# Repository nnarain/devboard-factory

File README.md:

# Dev boards and breakouts

This repo contains KiCAD projects for various dev boards and break outs

| Board    | Description          | Fabricated |
| -----    | -----------          | ---------- |
| xdevrf01 | STM32 + nRF24 module | No         |
| xdevrf02 | nRF52 + PCB Antenna  | No         |
| xdevrf03 | ESP32-C3-MINI        | Yes        |
| brkcan01 | SN65HVD232           | No         |

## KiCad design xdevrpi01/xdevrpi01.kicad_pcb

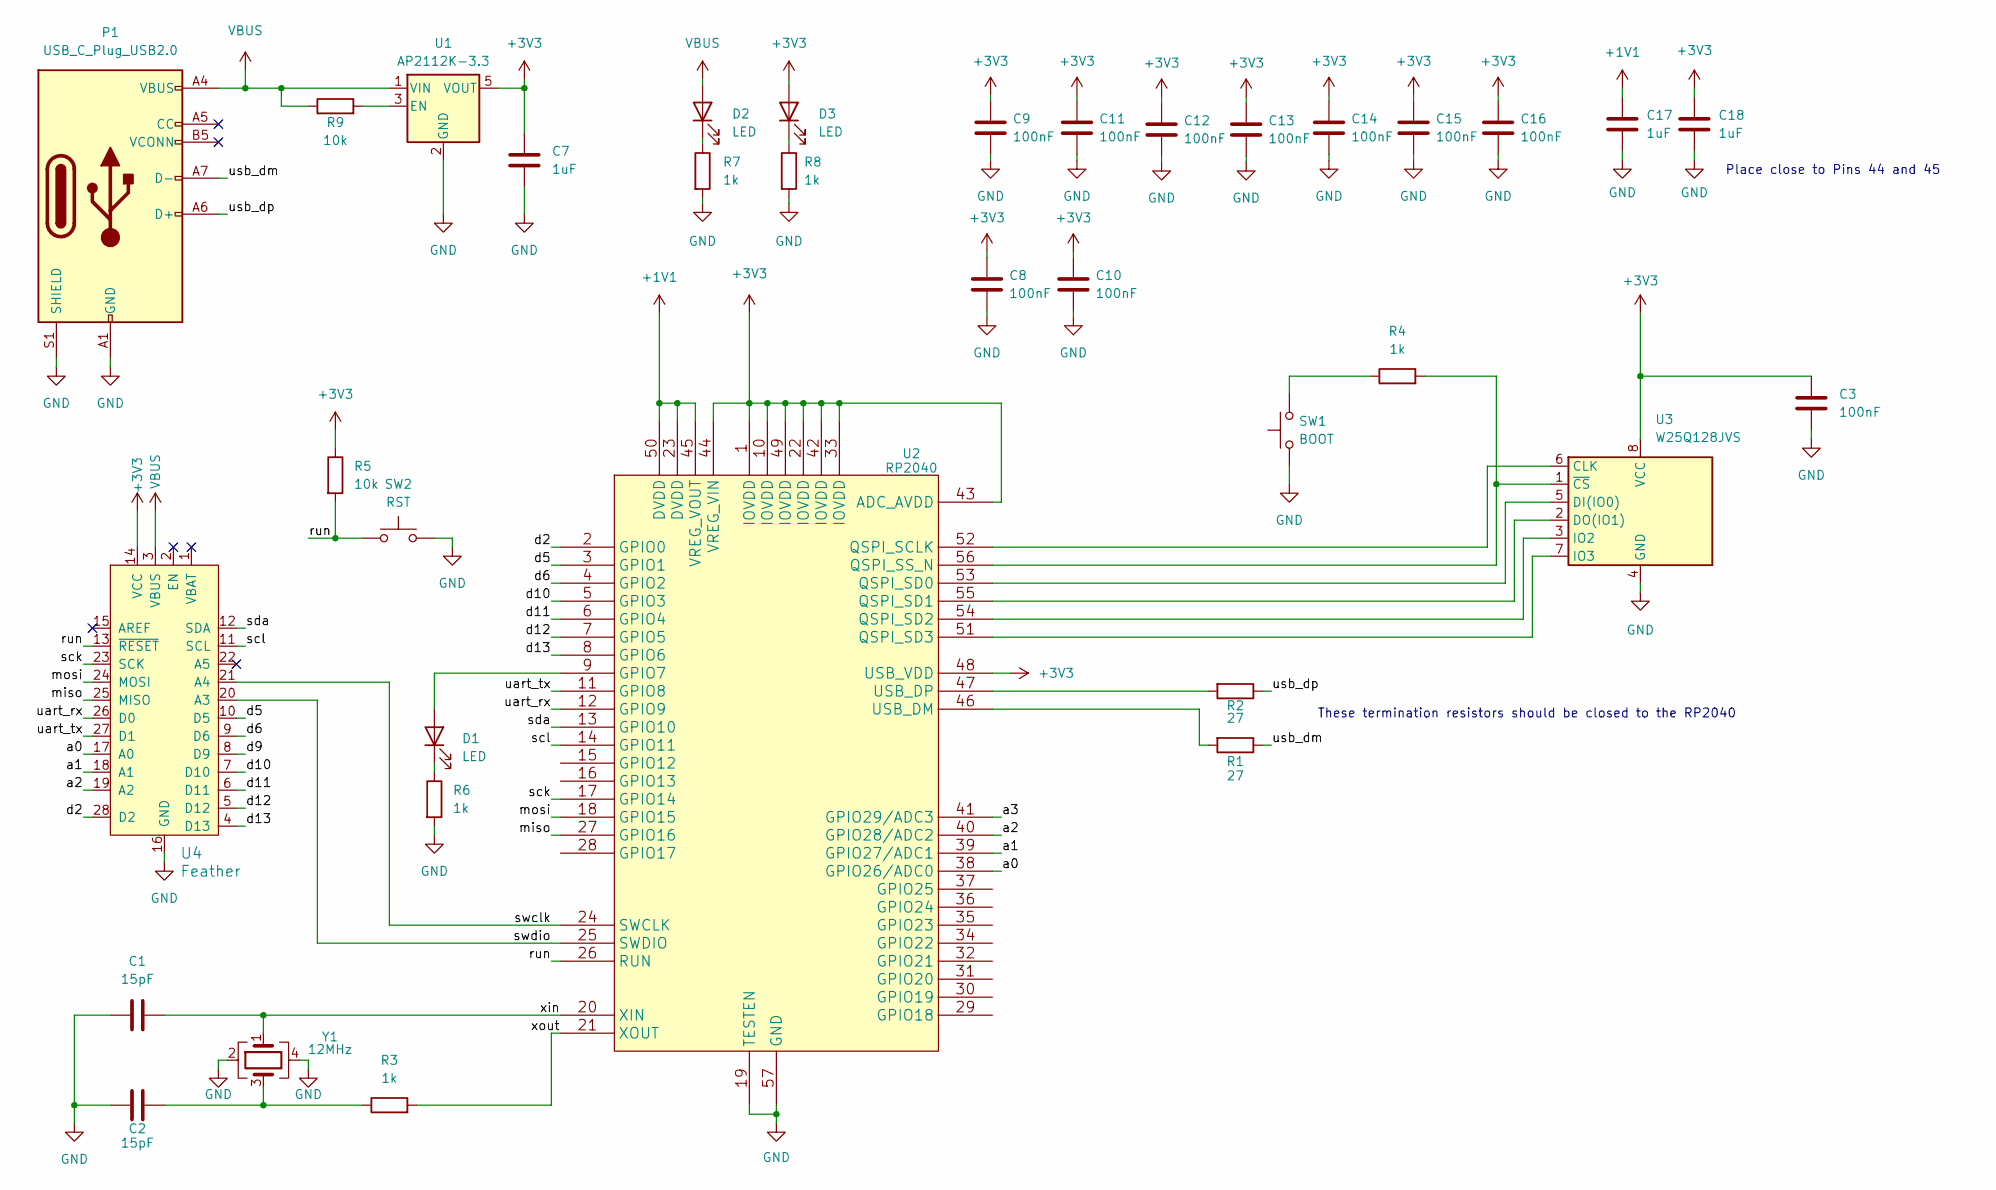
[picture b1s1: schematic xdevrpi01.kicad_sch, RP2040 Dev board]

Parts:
C1, C2: 15pF; C_0402_1005Metric; LCSC C326803
C3, C8, C9, C10, C11, C12, C13, C14, C15, C16: 100nF; C_0402_1005Metric; LCSC C307331
C7, C17, C18: 1uF; C_0402_1005Metric; LCSC C52923
D1: LED; LED_0603_1608Metric
D2, D3: LED; LED_0603_1608Metric; LCSC C72043
P1: USB_C_Plug_USB2.0; TYPE-C-31-M-04; LCSC C129018
R1, R2: 27; R_0402_1005Metric; LCSC C138021
R3, R4, R6, R7, R8: 1k; R_0402_1005Metric; LCSC C25543
R5, R9: 10k; R_0402_1005Metric; LCSC C25744
SW1: BOOT; TS-1088-AR02016; LCSC C720477
SW2: RST; TS-1088-AR02016; LCSC C720477
U1: AP2112K-3.3; SOT-23-5; LCSC C51118
U2: RP2040; LCSC C2040
U3: W25Q128JVS; SOIC-8_5.23x5.23mm_P1.27mm; LCSC C97521
U4: Feather; Feather_Main
Y1: 12MHz; Crystal_SMD_3225-4Pin_3.2x2.5mm; LCSC C20625731

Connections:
+1V1: C17.1, U2.23 (DVDD), U2.45 (VREG_VOUT), U2.50 (DVDD)
+3V3: C3.1, C7.1, C8.1, C9.1, C10.1, C11.1, C12.1, C13.1, C14.1, C15.1, C16.1, C18.1, D3.2 (A), R5.1, U1.5 (VOUT), U2.1 (IOVDD), U2.10 (IOVDD), U2.22 (IOVDD), U2.33 (IOVDD), U2.42 (IOVDD), U2.43 (ADC_AVDD), U2.44 (VREG_VIN), U2.48 (USB_VDD), U2.49 (IOVDD), U3.8 (VCC), U4.14 (VCC)
/a0: U2.38 (GPIO26/ADC0), U4.17 (A0)
/a1: U2.39 (GPIO27/ADC1), U4.18 (A1)
/a2: U2.40 (GPIO28/ADC2), U4.19 (A2)
/a3: U2.41 (GPIO29/ADC3)
/d2: U2.2 (GPIO0), U4.28 (D2)
/d5: U2.3 (GPIO1), U4.10 (D5)
/d6: U2.4 (GPIO2), U4.9 (D6)
/d9: U4.8 (D9)
/d10: U2.5 (GPIO3), U4.7 (D10)
/d11: U2.6 (GPIO4), U4.6 (D11)
/d12: U2.7 (GPIO5), U4.5 (D12)
/d13: U2.8 (GPIO6), U4.4 (D13)
/miso: U2.27 (GPIO16), U4.25 (MISO)
/mosi: U2.18 (GPIO15), U4.24 (MOSI)
/run: R5.2, SW2.1, U2.26 (RUN), U4.13 (~RESET)
/sck: U2.17 (GPIO14), U4.23 (SCK)
/scl: U2.14 (GPIO11), U4.11 (SCL)
/sda: U2.13 (GPIO10), U4.12 (SDA)
/swclk: U2.24 (SWCLK), U4.21 (A4)
/swdio: U2.25 (SWDIO), U4.20 (A3)
/uart_rx: U2.12 (GPIO9), U4.26 (D0)
/uart_tx: U2.11 (GPIO8), U4.27 (D1)
/usb_dm: P1.A7 (D-), R1.1
/usb_dp: P1.A6 (D+), R2.1
/xin: C1.2, U2.20 (XIN), Y1.1
/xout: R3.2, U2.21 (XOUT)
GND: C1.1, C2.1, C3.2, C7.2, C8.2, C9.2, C10.2, C11.2, C12.2, C13.2, C14.2, C15.2, C16.2, C17.2, C18.2, P1.A1 (GND), P1.A12 (GND), P1.B1 (GND), P1.B12 (GND), P1.S1 (SHIELD), R6.2, R7.2, R8.2, SW1.1, SW2.2, U1.2 (GND), U2.19 (TESTEN), U2.57 (GND), U3.4 (GND), U4.16 (GND), Y1.2, Y1.4
unnamed: C2.2, R3.1, Y1.3
unnamed: D1.2 (A), U2.9 (GPIO7)
unnamed: D1.1 (K), R6.1
unnamed: D2.1 (K), R7.1
unnamed: D3.1 (K), R8.1
unnamed: R4.1, SW1.2
unnamed: R9.2, U1.3 (EN)
unnamed: U2.52 (QSPI_SCLK), U3.6 (CLK)
unnamed: U2.53 (QSPI_SD0), U3.5 (DI(IO0))
unnamed: U2.55 (QSPI_SD1), U3.2 (DO(IO1))
unnamed: U2.54 (QSPI_SD2), U3.3 (IO2)
unnamed: U2.51 (QSPI_SD3), U3.7 (IO3)
unnamed: R4.2, U2.56 (QSPI_SS_N), U3.1 (~CS)
unnamed: R1.2, U2.46 (USB_DM)
unnamed: R2.2, U2.47 (USB_DP)
VBUS: D2.2 (A), P1.A4 (VBUS), P1.A9 (VBUS), P1.B4 (VBUS), P1.B9 (VBUS), R9.1, U1.1 (VIN), U4.3 (VBUS)

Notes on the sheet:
These termination resistors should be closed to the RP2040
Place close to Pins 44 and 45

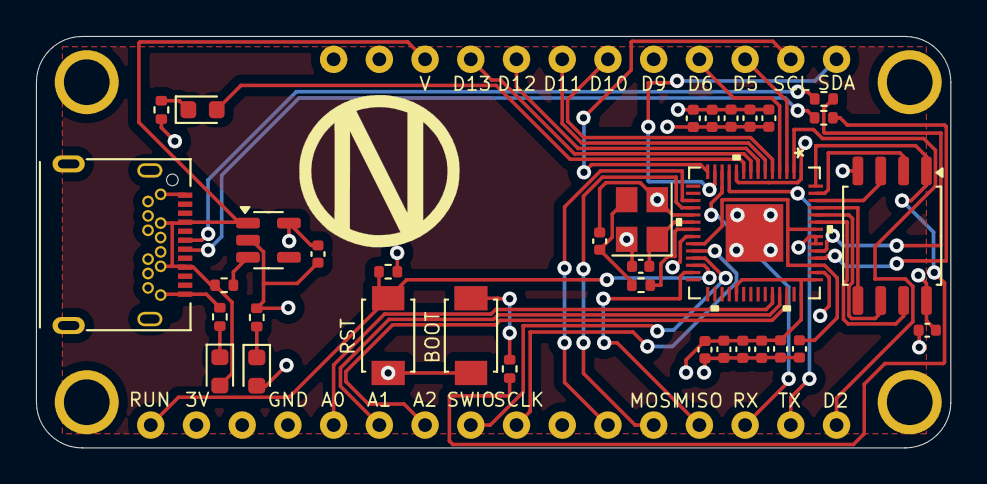
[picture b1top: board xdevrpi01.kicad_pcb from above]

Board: 4 copper layers, 50.8 x 22.9 mm, 35 parts (0 on the bottom side), 43 nets.

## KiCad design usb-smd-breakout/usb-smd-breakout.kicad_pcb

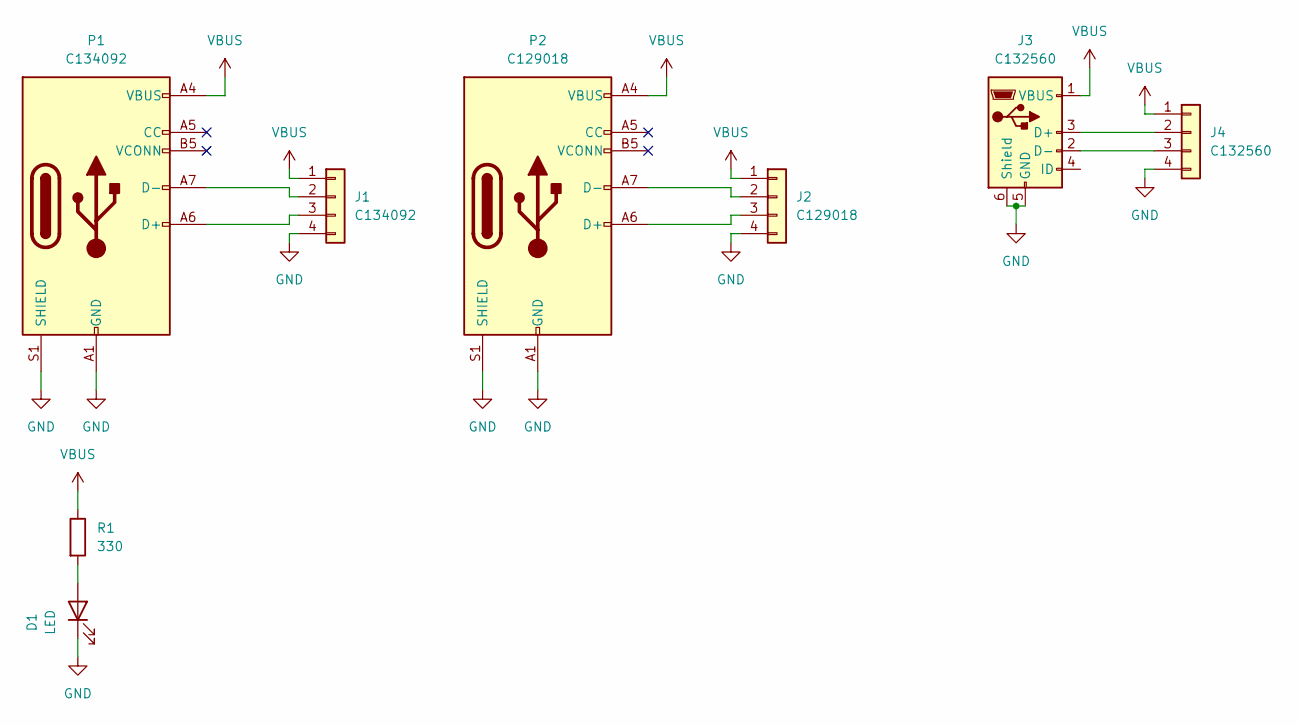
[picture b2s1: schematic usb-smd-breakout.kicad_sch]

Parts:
D1: LED; LED_0805_2012Metric; LCSC C434432
J1: C134092; PinSocket_1x04_P2.54mm_Vertical
J2: C129018; PinSocket_1x04_P2.54mm_Vertical
J3: C132560; USB_Micro-B_Molex_47346-0001; LCSC C132560
J4: C132560; PinSocket_1x04_P2.54mm_Vertical
P1: C134092; MOLEX_105450-0101; LCSC C134092
P2: C129018; TYPE-C-31-M-14; LCSC C129018
R1: 330; R_0805_2012Metric; LCSC C17630

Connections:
GND: D1.1 (K), J1.4, J2.4, J3.5 (GND), J3.6 (Shield), J4.4, P1.A1 (GND), P1.A12 (GND), P1.B1 (GND), P1.B12 (GND), P1.S1 (SHIELD), P2.A1 (GND), P2.A12 (GND), P2.B1 (GND), P2.B12 (GND), P2.S1 (SHIELD)
unnamed: D1.2 (A), R1.2
unnamed: J1.2, P1.A7 (D-)
unnamed: J1.3, P1.A6 (D+)
unnamed: J2.2, P2.A7 (D-)
unnamed: J2.3, P2.A6 (D+)
unnamed: J3.2 (D-), J4.3
unnamed: J3.3 (D+), J4.2
VBUS: J1.1, J2.1, J3.1 (VBUS), J4.1, P1.A4 (VBUS), P1.A9 (VBUS), P1.B4 (VBUS), P1.B9 (VBUS), P2.A4 (VBUS), P2.A9 (VBUS), P2.B4 (VBUS), P2.B9 (VBUS), R1.1

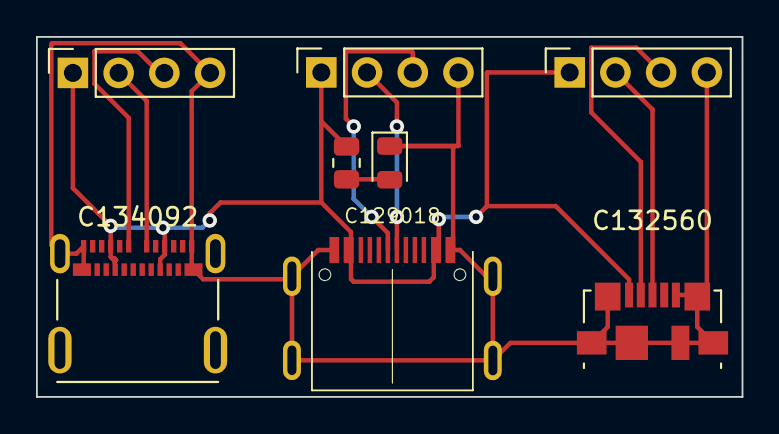
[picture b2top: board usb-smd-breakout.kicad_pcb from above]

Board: 2 copper layers, 39.2 x 20.0 mm, 8 parts (0 on the bottom side), 9 nets.

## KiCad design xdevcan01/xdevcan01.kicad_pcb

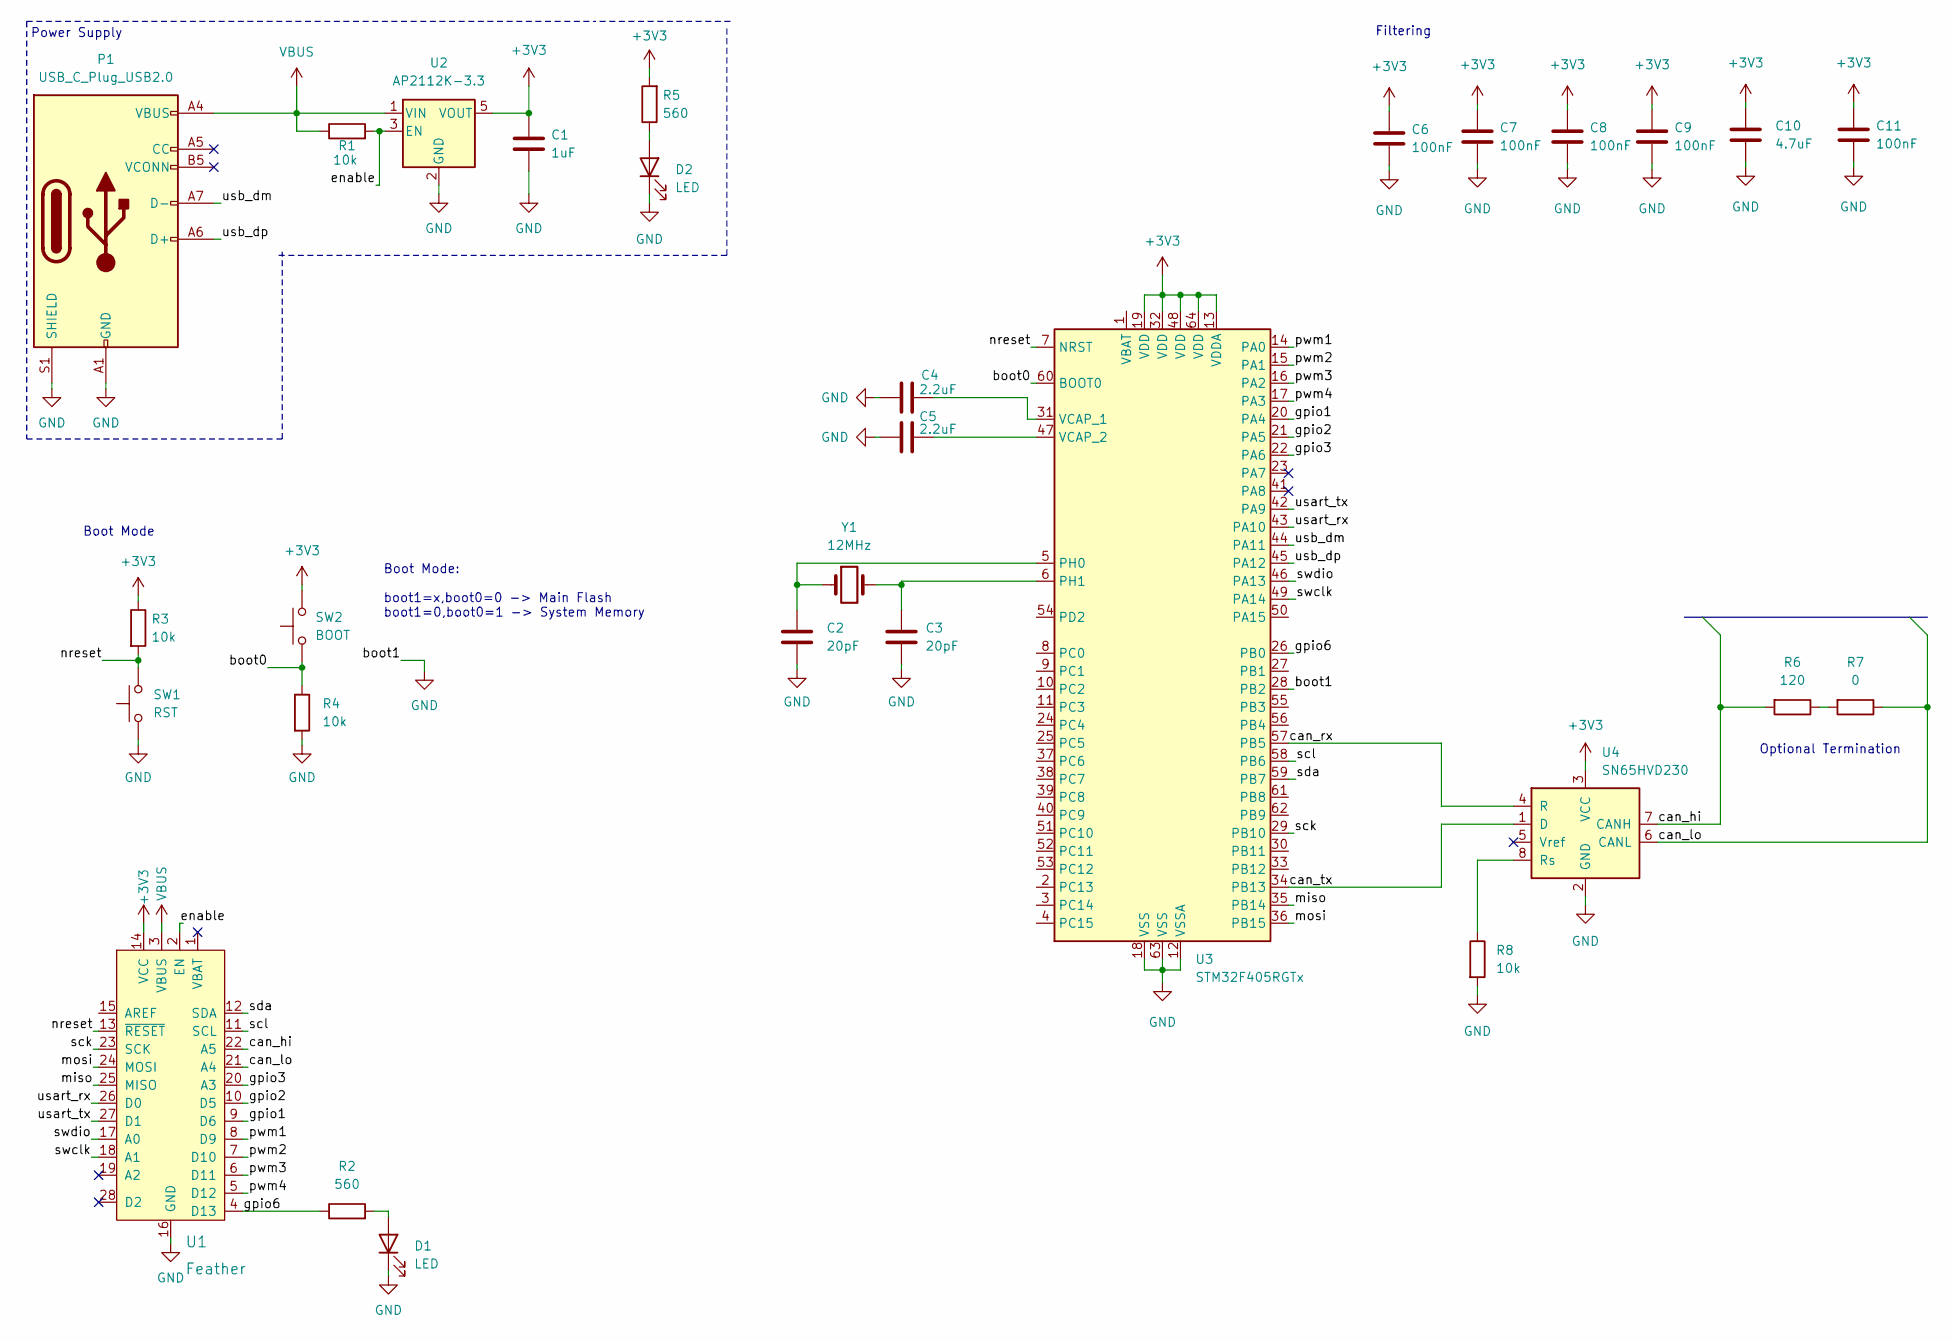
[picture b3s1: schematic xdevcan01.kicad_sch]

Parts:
C1: 1uF; C_0402_1005Metric; LCSC C52923
C2, C3: 20pF; C_0402_1005Metric; LCSC C1554
C4, C5: 2.2uF; C_0402_1005Metric; LCSC C12530
C6, C7, C8, C9, C11: 100nF; C_0402_1005Metric; LCSC C307331
C10: 4.7uF; C_0402_1005Metric; LCSC C23733
D1: LED; LED_0603_1608Metric; LCSC C72041
D2: LED; LED_0603_1608Metric; LCSC C72043
P1: USB_C_Plug_USB2.0; TYPE-C-31-M-04; LCSC C129018
R1, R3, R4, R8: 10k; R_0402_1005Metric; LCSC C25744
R2, R5: 560; R_0402_1005Metric; LCSC C25172
R6: 120; R_0402_1005Metric; LCSC C445577
R7: 0; SolderJumper-2_P1.3mm_Open_TrianglePad1.0x1.5mm
SW1: RST; TS-1088-AR02016; LCSC C720477
SW2: BOOT; TS-1088-AR02016; LCSC C720477
U1: Feather; Feather_Main
U2: AP2112K-3.3; SOT-23-5; LCSC C51118
U3: STM32F405RGTx; LQFP-64_10x10mm_P0.5mm; LCSC C15742
U4: SN65HVD230; SOIC-8_3.9x4.9mm_P1.27mm; LCSC C12084
Y1: 12MHz; Crystal_SMD_3225-4Pin_3.2x2.5mm; LCSC C9002

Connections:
+3V3: C1.1, C6.1, C7.1, C8.1, C9.1, C10.1, C11.1, R3.1, R5.2, SW2.2, U1.14 (VCC), U2.5 (VOUT), U3.13 (VDDA), U3.19 (VDD), U3.32 (VDD), U3.48 (VDD), U3.64 (VDD), U4.3 (VCC)
/boot0: R4.1, SW2.1, U3.60 (BOOT0)
/can_hi: R6.2, U1.22 (A5), U4.7 (CANH)
/can_lo: R7.1, U1.21 (A4), U4.6 (CANL)
/can_rx: U3.57 (PB5), U4.4 (R)
/can_tx: U3.34 (PB13), U4.1 (D)
/enable: R1.2, U1.2 (EN), U2.3 (EN)
/gpio1: U1.9 (D6), U3.20 (PA4)
/gpio2: U1.10 (D5), U3.21 (PA5)
/gpio3: U1.20 (A3), U3.22 (PA6)
/gpio4: U3.23 (PA7)
/gpio5: U3.41 (PA8)
/gpio6: R2.1, U1.4 (D13), U3.26 (PB0)
/miso: U1.25 (MISO), U3.35 (PB14)
/mosi: U1.24 (MOSI), U3.36 (PB15)
/nreset: R3.2, SW1.2, U1.13 (~RESET), U3.7 (NRST)
/pwm1: U1.8 (D9), U3.14 (PA0)
/pwm2: U1.7 (D10), U3.15 (PA1)
/pwm3: U1.6 (D11), U3.16 (PA2)
/pwm4: U1.5 (D12), U3.17 (PA3)
/sck: U1.23 (SCK), U3.29 (PB10)
/scl: U1.11 (SCL), U3.58 (PB6)
/sda: U1.12 (SDA), U3.59 (PB7)
/swclk: U1.18 (A1), U3.49 (PA14)
/swdio: U1.17 (A0), U3.46 (PA13)
/usart_rx: U1.26 (D0), U3.43 (PA10)
/usart_tx: U1.27 (D1), U3.42 (PA9)
/usb_dm: P1.A7 (D-), U3.44 (PA11)
/usb_dp: P1.A6 (D+), U3.45 (PA12)
GND: C1.2, C2.2, C3.2, C4.2, C5.2, C6.2, C7.2, C8.2, C9.2, C10.2, C11.2, D1.1 (K), D2.1 (K), P1.A1 (GND), P1.A12 (GND), P1.B1 (GND), P1.B12 (GND), P1.S1 (SHIELD), R4.2, R8.2, SW1.1, U1.16 (GND), U2.2 (GND), U3.12 (VSSA), U3.18 (VSS), U3.28 (PB2), U3.63 (VSS), U4.2 (GND)
unnamed: D1.2 (A), R2.2
unnamed: D2.2 (A), R5.1
unnamed: R6.1, R7.2
unnamed: C2.1, U3.5 (PH0), Y1.1
unnamed: C3.1, U3.6 (PH1), Y1.2
unnamed: C4.1, U3.31 (VCAP_1)
unnamed: C5.1, U3.47 (VCAP_2)
unnamed: R8.1, U4.8 (Rs)
VBUS: P1.A4 (VBUS), P1.A9 (VBUS), P1.B4 (VBUS), P1.B9 (VBUS), R1.1, U1.3 (VBUS), U2.1 (VIN)

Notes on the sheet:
Optional Termination
Boot Mode
Boot Mode: boot1=x,boot0=0 -> Main Flash boot1=0,boot0=1 -> System Memory
Power Supply
Filtering

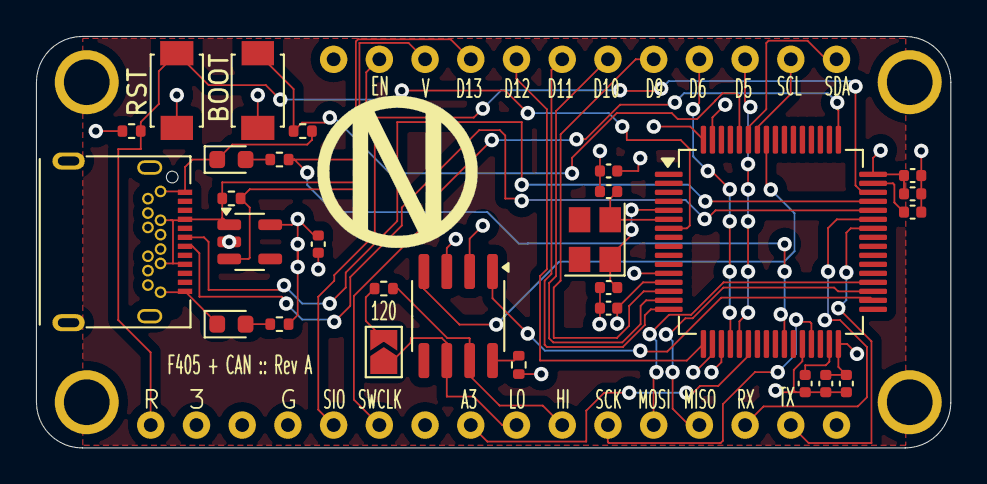
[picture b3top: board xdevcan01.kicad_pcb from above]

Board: 4 copper layers, 50.8 x 22.9 mm, 29 parts (0 on the bottom side), 37 nets.

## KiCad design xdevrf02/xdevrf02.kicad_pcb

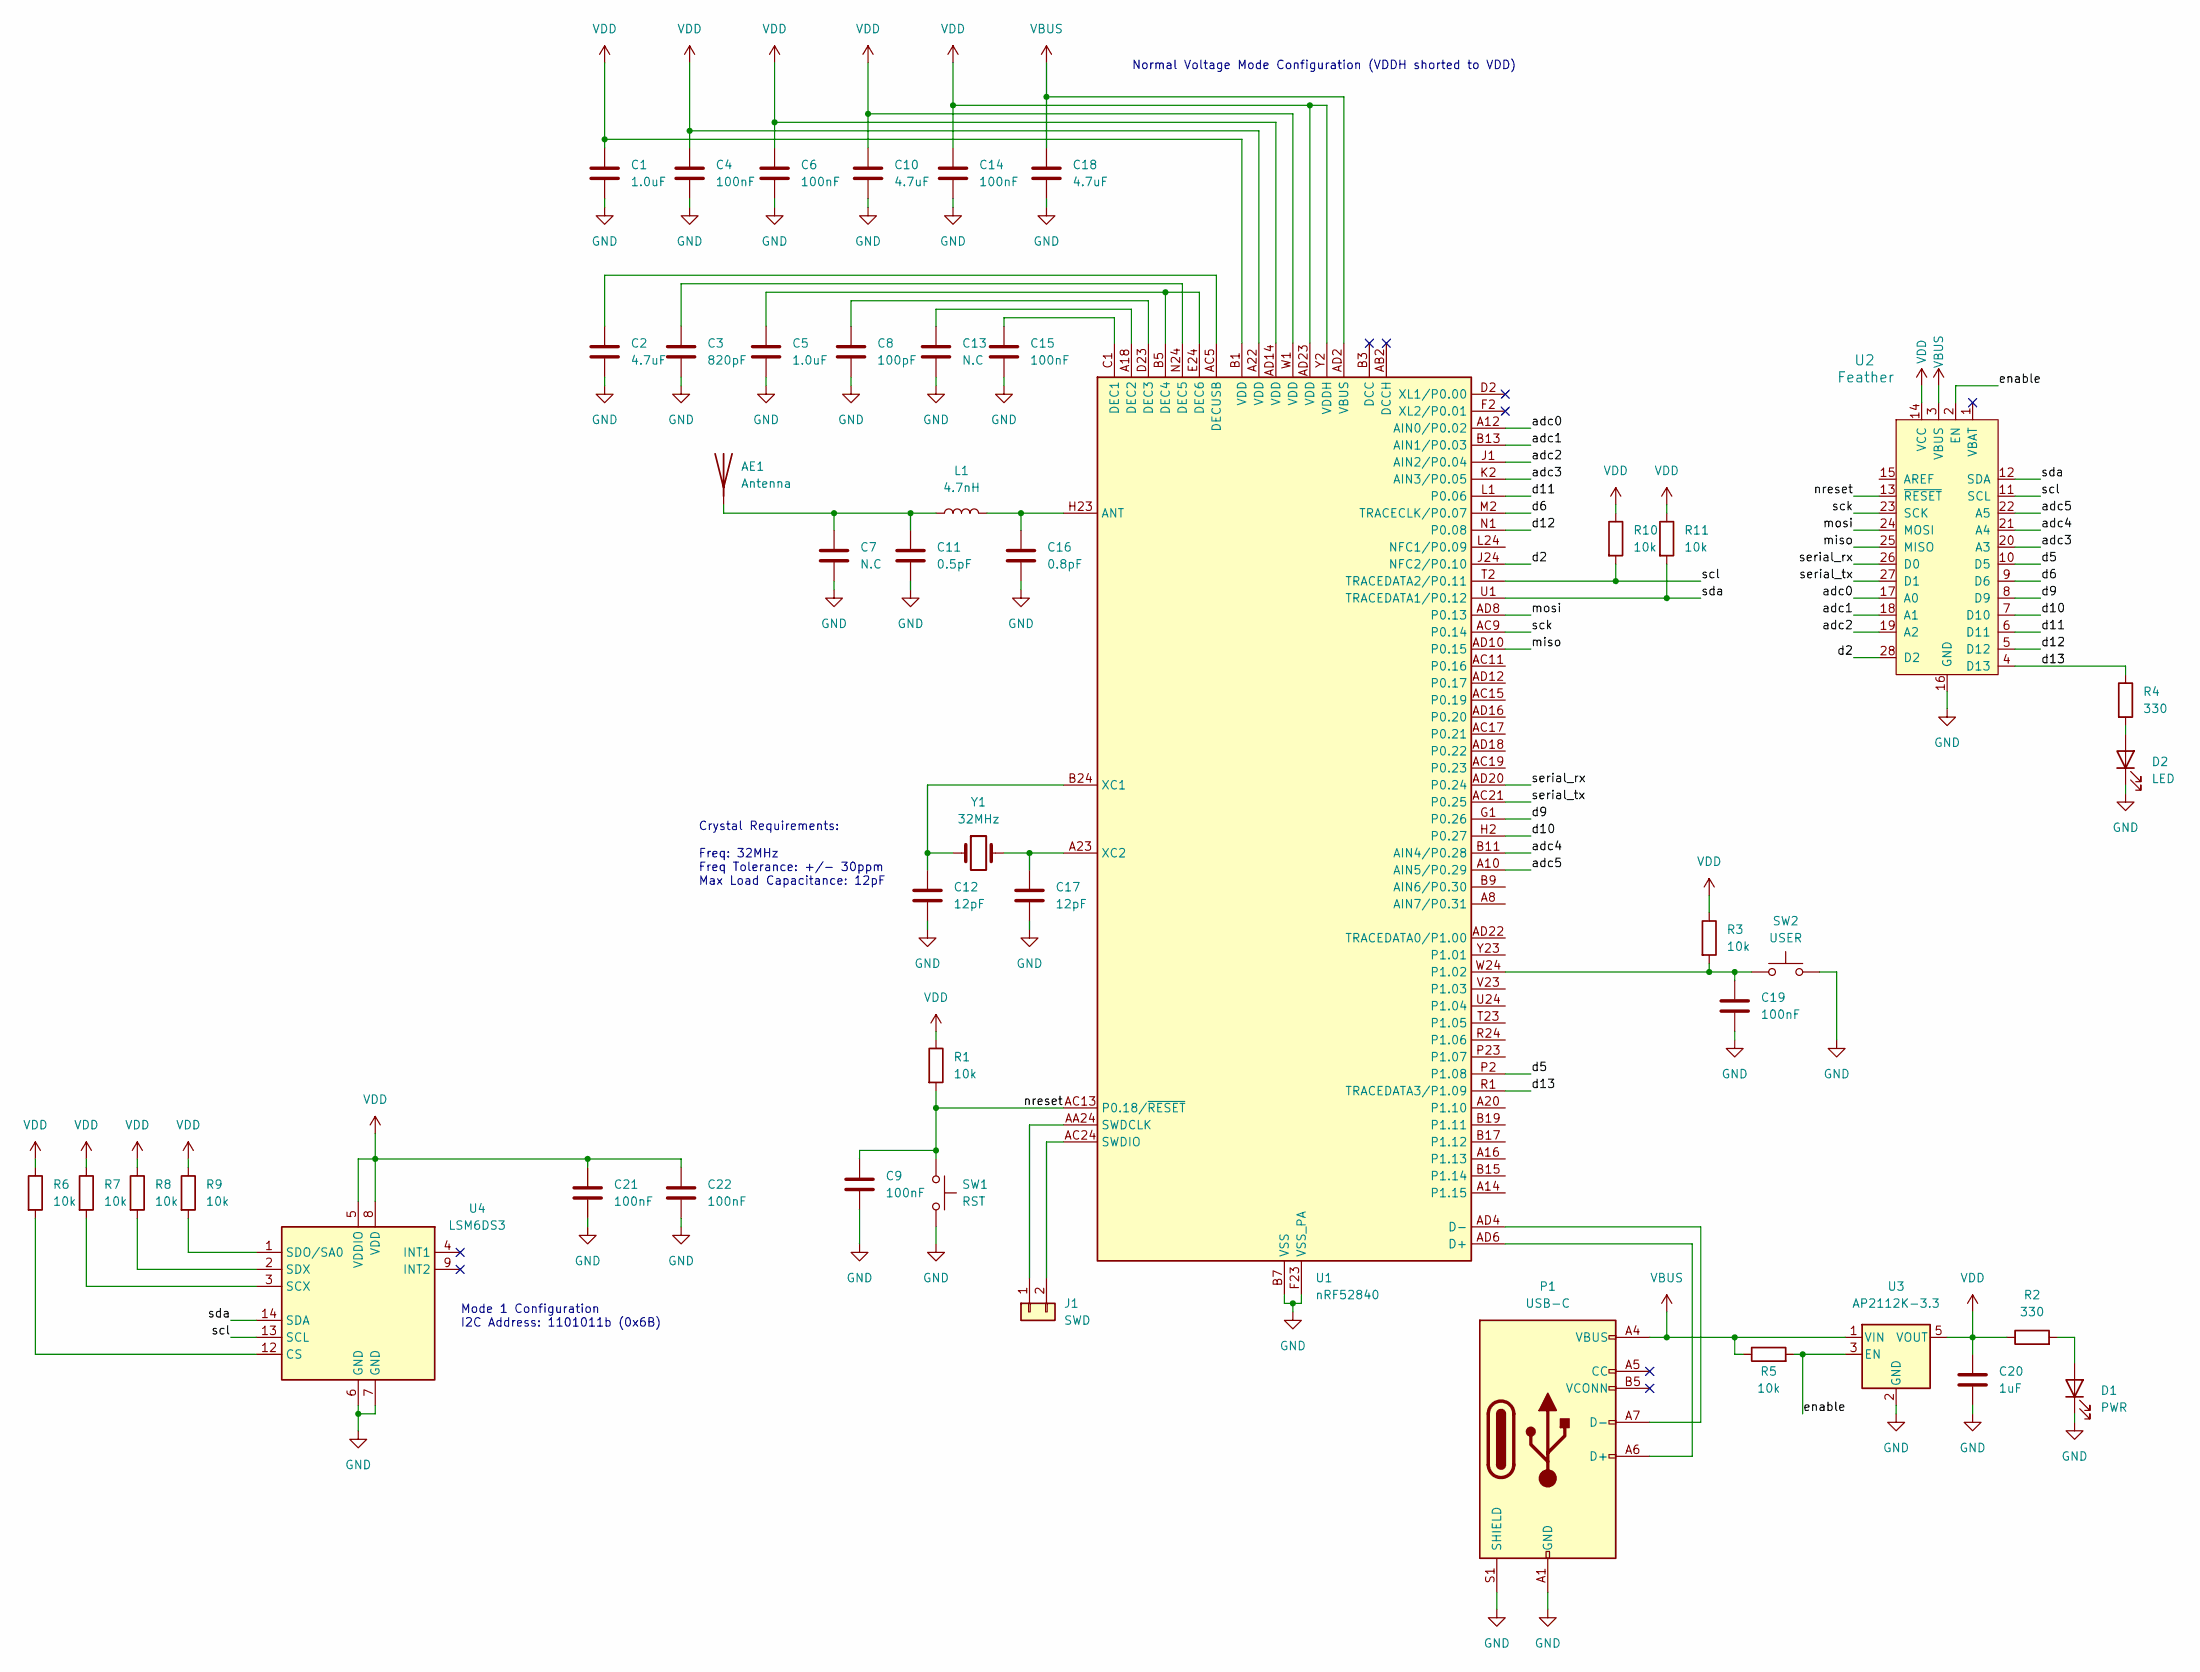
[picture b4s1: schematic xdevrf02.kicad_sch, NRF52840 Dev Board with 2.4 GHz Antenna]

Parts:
AE1: Antenna; Texas_SWRA117D_2.4GHz_Right
C1, C5: 1.0uF; C_0402_1005Metric
C2, C10, C18: 4.7uF; C_0402_1005Metric
C3: 820pF; C_0402_1005Metric
C4, C6, C9, C14, C15, C19, C21, C22: 100nF; C_0402_1005Metric
C7, C13: N.C; C_0402_1005Metric
C8: 100pF; C_0402_1005Metric
C11: 0.5pF; C_0402_1005Metric
C12, C17: 12pF; C_0402_1005Metric
C16: 0.8pF; C_0402_1005Metric
C20: 1uF; C_0402_1005Metric
D1: PWR; LED_0603_1608Metric; LCSC C2286
D2: LED; LED_0603_1608Metric; LCSC C72041
J1: SWD; PinHeader_1x02_P2.54mm_Vertical
L1: 4.7nH; L_0402_1005Metric
P1: USB-C; TYPE-C-31-M-04
R1, R3, R5: 10k; R_0402_1005Metric
R2, R4: 330; R_0402_1005Metric
R6, R7, R8, R9, R10, R11: 10k; C_0402_1005Metric
SW1: RST; TS-1088-AR02016
SW2: USER; TS-1088-AR02016
U1: nRF52840; Nordic_AQFN-73-1EP_7x7mm_P0.5mm; LCSC C190794
U2: Feather; Feather_Main
U3: AP2112K-3.3; SOT-23-5; LCSC C51118
U4: LSM6DS3; LGA-14_3x2.5mm_P0.5mm_LayoutBorder3x4y; LCSC C95230
Y1: 32MHz; Crystal_SMD_2016-4Pin_2.0x1.6mm; LCSC C187794

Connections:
/adc0: U1.A12 (AIN0/P0.02), U2.17 (A0)
/adc1: U1.B13 (AIN1/P0.03), U2.18 (A1)
/adc2: U1.J1 (AIN2/P0.04), U2.19 (A2)
/adc3: U1.K2 (AIN3/P0.05), U2.20 (A3)
/adc4: U1.B11 (AIN4/P0.28), U2.21 (A4)
/adc5: U1.A10 (AIN5/P0.29), U2.22 (A5)
/d2: U1.J24 (NFC2/P0.10), U2.28 (D2)
/d5: U1.P2 (P1.08), U2.10 (D5)
/d6: U1.M2 (TRACECLK/P0.07), U2.9 (D6)
/d9: U1.G1 (P0.26), U2.8 (D9)
/d10: U1.H2 (P0.27), U2.7 (D10)
/d11: U1.L1 (P0.06), U2.6 (D11)
/d12: U1.N1 (P0.08), U2.5 (D12)
/d13: R4.1, U1.R1 (TRACEDATA3/P1.09), U2.4 (D13)
/enable: R5.2, U2.2 (EN), U3.3 (EN)
/miso: U1.AD10 (P0.15), U2.25 (MISO)
/mosi: U1.AD8 (P0.13), U2.24 (MOSI)
/nreset: C9.1, R1.2, SW1.1, U1.AC13 (P0.18/~RESET), U2.13 (~RESET)
/sck: U1.AC9 (P0.14), U2.23 (SCK)
/scl: R10.2, U1.T2 (TRACEDATA2/P0.11), U2.11 (SCL), U4.13 (SCL)
/sda: R11.2, U1.U1 (TRACEDATA1/P0.12), U2.12 (SDA), U4.14 (SDA)
/serial_rx: U1.AD20 (P0.24), U2.26 (D0)
/serial_tx: U1.AC21 (P0.25), U2.27 (D1)
GND: C1.2, C2.2, C3.2, C4.2, C5.2, C6.2, C7.2, C8.2, C9.2, C10.2, C11.2, C12.2, C13.2, C14.2, C15.2, C16.2, C17.2, C18.2, C19.2, C20.2, C21.2, C22.2, D1.1 (K), D2.1 (K), P1.A1 (GND), P1.A12 (GND), P1.B1 (GND), P1.B12 (GND), P1.S1 (SHIELD), SW1.2, SW2.2, U1.B7 (VSS), U1.EP (VSS), U1.F23 (VSS_PA), U2.16 (GND), U3.2 (GND), U4.6 (GND), U4.7 (GND)
unnamed: AE1.1 (A), C7.1, C11.1, L1.1
unnamed: C2.1, U1.AC5 (DECUSB)
unnamed: C3.1, U1.N24 (DEC5)
unnamed: C5.1, U1.B5 (DEC4), U1.E24 (DEC6)
unnamed: C8.1, U1.D23 (DEC3)
unnamed: C12.1, U1.B24 (XC1), Y1.1
unnamed: C13.1, U1.A18 (DEC2)
unnamed: C15.1, U1.C1 (DEC1)
unnamed: C16.1, L1.2, U1.H23 (ANT)
unnamed: C17.1, U1.A23 (XC2), Y1.2
unnamed: D1.2 (A), R2.2
unnamed: D2.2 (A), R4.2
unnamed: J1.1, U1.AA24 (SWDCLK)
unnamed: J1.2, U1.AC24 (SWDIO)
unnamed: P1.A6 (D+), U1.AD6 (D+)
unnamed: P1.A7 (D-), U1.AD4 (D-)
unnamed: R6.2, U4.12 (CS)
unnamed: R7.2, U4.3 (SCX)
unnamed: R8.2, U4.2 (SDX)
unnamed: R9.2, U4.1 (SDO/SA0)
unnamed: C19.1, R3.2, SW2.1, U1.W24 (P1.02)
VBUS: C18.1, P1.A4 (VBUS), P1.A9 (VBUS), P1.B4 (VBUS), P1.B9 (VBUS), R5.1, U1.AD2 (VBUS), U2.3 (VBUS), U3.1 (VIN)
VDD: C1.1, C4.1, C6.1, C10.1, C14.1, C20.1, C21.1, C22.1, R1.1, R2.1, R3.1, R6.1, R7.1, R8.1, R9.1, R10.1, R11.1, U1.A22 (VDD), U1.AD14 (VDD), U1.AD23 (VDD), U1.B1 (VDD), U1.W1 (VDD), U1.Y2 (VDDH), U2.14 (VCC), U3.5 (VOUT), U4.5 (VDDIO), U4.8 (VDD)

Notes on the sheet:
Mode 1 Configuration I2C Address: 1101011b (0x6B)
Crystal Requirements: Freq: 32MHz Freq Tolerance: +/- 30ppm Max Load Capacitance: 12pF
Normal Voltage Mode Configuration (VDDH shorted to VDD)

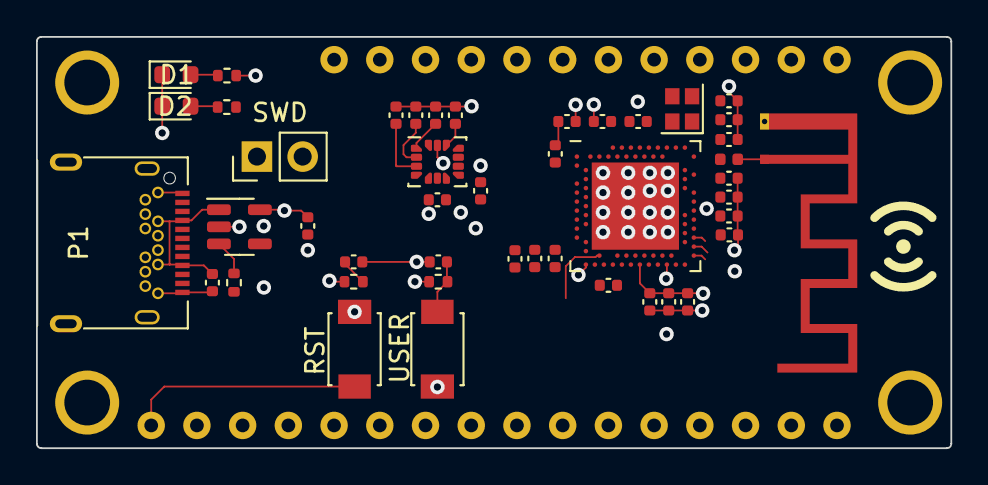
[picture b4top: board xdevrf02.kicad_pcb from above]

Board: 4 copper layers, 50.8 x 22.9 mm, 46 parts (0 on the bottom side), 47 nets.

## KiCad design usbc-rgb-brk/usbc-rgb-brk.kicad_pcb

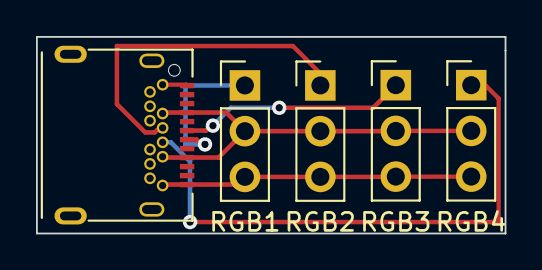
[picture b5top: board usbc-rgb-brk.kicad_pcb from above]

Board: 2 copper layers, 26.0 x 10.9 mm, 5 parts (0 on the bottom side), 6 nets.

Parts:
J1: USB_C_Receptacle; TYPE-C-31-M-04
J2: RGB1; PinHeader_1x03_P2.54mm_Vertical
J3: RGB2; PinHeader_1x03_P2.54mm_Vertical
J4: RGB3; PinHeader_1x03_P2.54mm_Vertical
J5: RGB4; PinHeader_1x03_P2.54mm_Vertical

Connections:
GND: J1.A1 (GND), J1.A12 (GND), J1.B1 (GND), J1.B12 (GND), J2.3, J3.3, J4.3, J5.3
unnamed: J1.A6 (D+), J4.1
unnamed: J1.A7 (D-), J2.1
unnamed: J1.B6 (D+), J5.1
unnamed: J1.B7 (D-), J3.1
VBUS: J1.A4 (VBUS), J1.A9 (VBUS), J1.B4 (VBUS), J1.B9 (VBUS), J2.2, J3.2, J4.2, J5.2

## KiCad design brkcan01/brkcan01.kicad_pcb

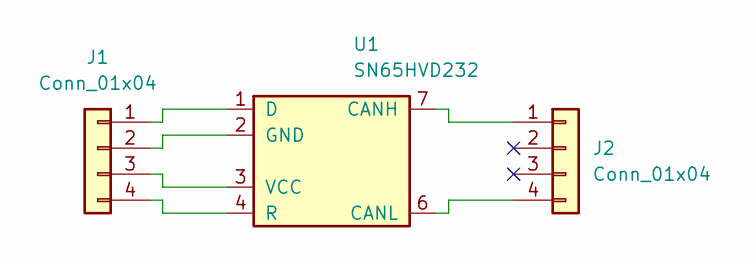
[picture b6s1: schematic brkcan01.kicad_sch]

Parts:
J1, J2: Conn_01x04; PinHeader_1x04_P2.54mm_Vertical
U1: SN65HVD232; SOIC-8_3.9x4.9mm_P1.27mm; LCSC C30530

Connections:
unnamed: J1.1, U1.1 (D)
unnamed: J1.2, U1.2 (GND)
unnamed: J1.3, U1.3 (VCC)
unnamed: J1.4, U1.4 (R)
unnamed: J2.1, U1.7 (CANH)
unnamed: J2.4, U1.6 (CANL)

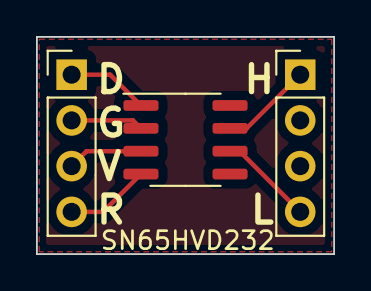
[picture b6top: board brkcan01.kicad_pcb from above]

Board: 2 copper layers, 16.5 x 12.1 mm, 3 parts (0 on the bottom side), 6 nets.

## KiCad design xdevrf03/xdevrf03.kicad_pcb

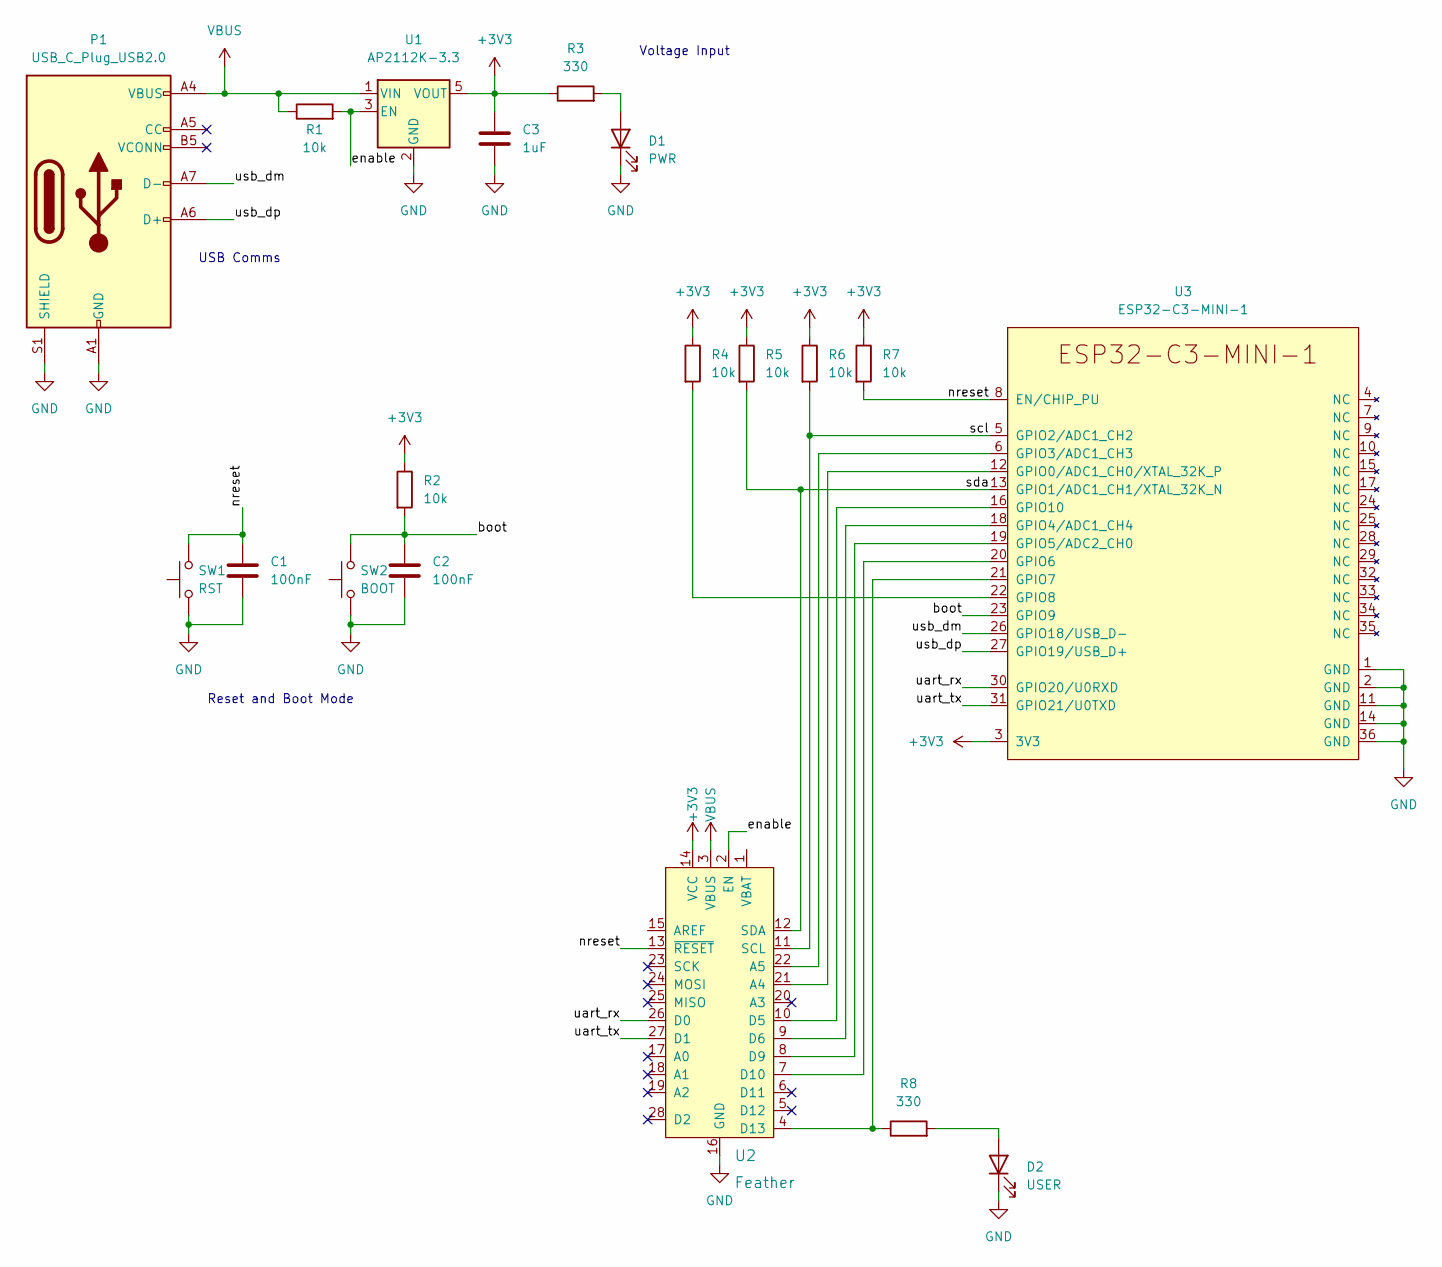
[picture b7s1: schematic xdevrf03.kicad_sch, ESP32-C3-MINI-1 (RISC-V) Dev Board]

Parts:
C1, C2: 100nF; C_0805_2012Metric; LCSC C28233
C3: 1uF; C_0805_2012Metric; LCSC C28323
D1: PWR; LED_0805_2012Metric; LCSC C434432
D2: USER; LED_0805_2012Metric; LCSC C138555
P1: USB_C_Plug_USB2.0; TYPE-C-31-M-04; LCSC C129018
R1, R2, R4, R5, R6, R7: 10k; R_0805_2012Metric; LCSC C17414
R3, R8: 330; R_0805_2012Metric; LCSC C17630
SW1: RST; TS-1088-AR02016; LCSC C720477
SW2: BOOT; TS-1088-AR02016; LCSC C720477
U1: AP2112K-3.3; SOT-23-5; LCSC C51118
U2: Feather; Feather_Main
U3: ESP32-C3-MINI-1; LCSC C2838502

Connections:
+3V3: C3.1, R2.1, R3.1, R4.1, R5.1, R6.1, R7.1, U1.5 (VOUT), U2.14 (VCC), U3.3 (3V3)
/boot: C2.1, R2.2, SW2.2, U3.23 (GPIO9)
/enable: R1.2, U1.3 (EN), U2.2 (EN)
/nreset: C1.1, R7.2, SW1.2, U2.13 (~RESET), U3.8 (EN/CHIP_PU)
/scl: R6.2, U2.11 (SCL), U3.5 (GPIO2/ADC1_CH2)
/sda: R5.2, U2.12 (SDA), U3.13 (GPIO1/ADC1_CH1/XTAL_32K_N)
/uart_rx: U2.26 (D0), U3.30 (GPIO20/U0RXD)
/uart_tx: U2.27 (D1), U3.31 (GPIO21/U0TXD)
/usb_dm: P1.A7 (D-), U3.26 (GPIO18/USB_D-)
/usb_dp: P1.A6 (D+), U3.27 (GPIO19/USB_D+)
GND: C1.2, C2.2, C3.2, D1.1 (K), D2.1 (K), P1.A1 (GND), P1.A12 (GND), P1.B1 (GND), P1.B12 (GND), P1.S1 (SHIELD), SW1.1, SW2.1, U1.2 (GND), U2.16 (GND), U3.1 (GND), U3.2 (GND), U3.11 (GND), U3.14 (GND), U3.36 (GND)
unnamed: D1.2 (A), R3.2
unnamed: D2.2 (A), R8.2
unnamed: R4.2, U3.22 (GPIO8)
unnamed: R8.1, U2.4 (D13), U3.21 (GPIO7)
unnamed: U2.7 (D10), U3.20 (GPIO6)
unnamed: U2.8 (D9), U3.19 (GPIO5/ADC2_CH0)
unnamed: U2.9 (D6), U3.18 (GPIO4/ADC1_CH4)
unnamed: U2.10 (D5), U3.16 (GPIO10)
unnamed: U2.21 (A4), U3.12 (GPIO0/ADC1_CH0/XTAL_32K_P)
unnamed: U2.22 (A5), U3.6 (GPIO3/ADC1_CH3)
VBUS: P1.A4 (VBUS), P1.A9 (VBUS), P1.B4 (VBUS), P1.B9 (VBUS), R1.1, U1.1 (VIN), U2.3 (VBUS)

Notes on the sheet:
Voltage Input
USB Comms
Reset and Boot Mode

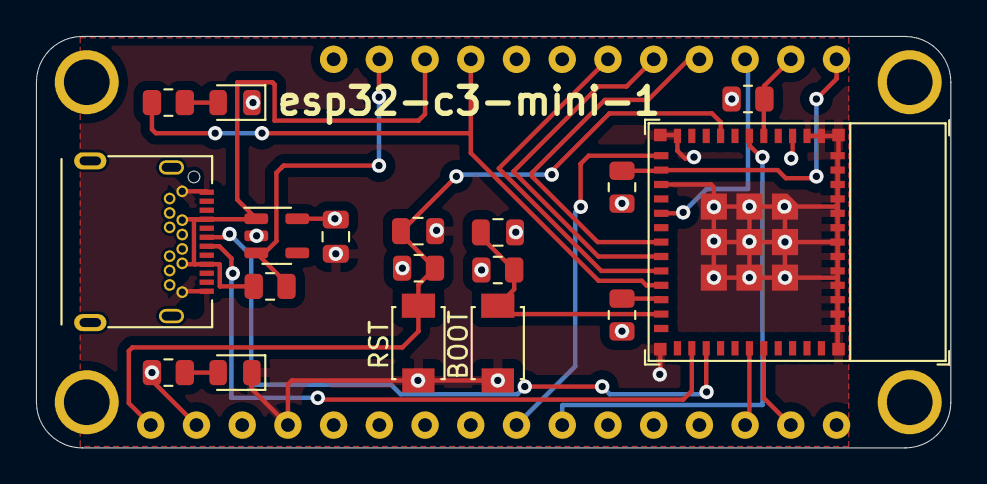
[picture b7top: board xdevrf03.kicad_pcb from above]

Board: 4 copper layers, 50.8 x 22.9 mm, 19 parts (0 on the bottom side), 22 nets.

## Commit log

2022-05-04 Added kicad-inventory
2022-05-05 USB SMD Breakout with JLCPCB part selection
2022-05-16 xdevrf01 schematic
2022-06-04 nrf52840 schematic
2022-06-05 ESP32-C3-MINI-1 devboard
2022-06-05 Added kibot and common config
2022-06-05 Schematic updates and pcb silkscreen
2022-06-11 test
2022-06-11 build,yml
2022-06-11 more tests
2022-06-11 deploy: 8b12e2ed182b914c4b979d9c5846dcf9a02b542e
2022-06-12 docs
2022-06-12 Clean up workflow trigger
2022-06-12 deploy: fba8f1de7f34e4f7e7225160a3c8e9c8f1d4fd0c
2022-06-12 deploy: a7d1bf625c4370ce94376344c4b8a6776e36cd70
2022-06-12 Update render outputs
2022-06-12 deploy: de07a3354c4c93e6433787c83e421016993aac50
2022-06-13 CAN breakout board
2022-06-13 deploy: 1b72d4ee8ecef0ea9439e7868882aaa911ad2034
2022-06-13 Update docs
2022-06-13 deploy: 3f9cf7bee80d80eb74b9b35048d35072c88f160f
2022-06-14 Updates to CAN breakout
2022-06-14 deploy: f97ae327defa784da9500f5ede5e5e6af3e2d05c
2022-09-11 USB RGB Breakout
2022-09-11 deploy: ded88f384dcb8caf7cb75782f5b9d15586306651
2023-02-24 design rules
2023-02-24 deploy: 179b255816bc3682ce063f0c77e0493fc17ae6d8
2023-04-02 rp2040 sch
2023-04-02 deploy: a945ec7842e51c579083c9c65078c339a27d2121
2023-04-10 STM32F405 Dev Board
2023-04-10 Update CI build
2023-04-10 Bump kibot action version to v2
2023-04-10 Specify exact sch and pcb file
2023-04-10 deploy: 403e3ac19fa25838d742e1a28ee1e1e3b85a33ba
2024-09-29 CAN devboard
2024-12-28 xdevrpi01
2024-12-28 update github action workflow
2024-12-28 added rpi kibot config
2024-12-28 update kicad version to v8
2024-12-28 update xdevstm01 crystal datasheet
2024-12-28 checkout
2024-12-28 configure pages
2024-12-29 update rp2040 footprint
2025-01-12 fix regulator pin
2025-01-12 adjust switch text

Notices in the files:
parts and their libraries:
Copyright 2021 Accelerated Designs. All rights reserved.
